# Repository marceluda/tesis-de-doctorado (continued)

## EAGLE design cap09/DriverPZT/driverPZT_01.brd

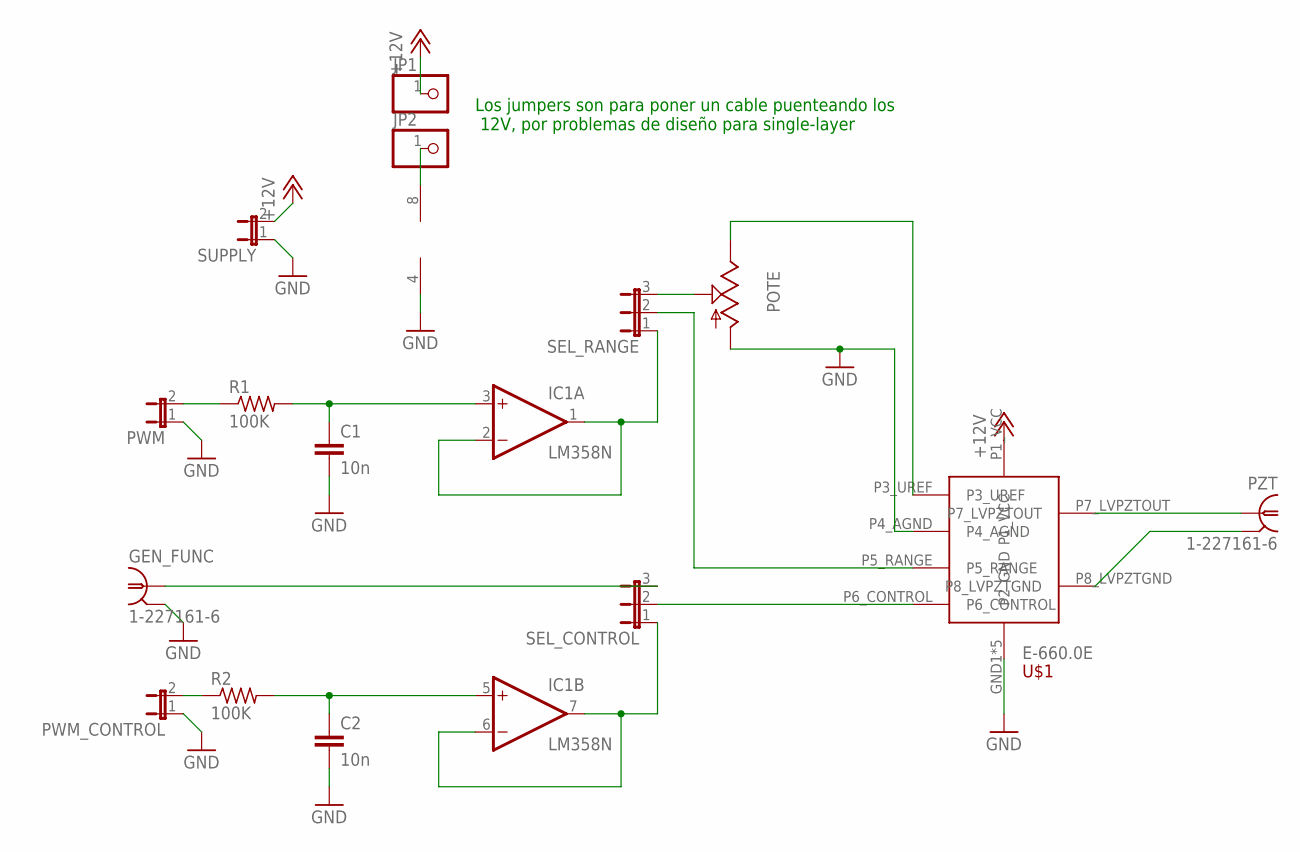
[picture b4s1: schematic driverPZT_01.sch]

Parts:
C1, C2: 10n; C050-075X075
GEN_FUNC: 1-227161-6; AMP_227161
IC1: LM358N; DIL08
JP1, JP2: PINHD-1X1; 1X01
POTE: TRIM_US-B64Y; B64Y
PWM: JP1E; JP1
PWM_CONTROL: JP1E; JP1
PZT: 1-227161-6; AMP_227161
R1, R2: 100K; 0207/12
SEL_CONTROL: JP2E; JP2
SEL_RANGE: JP2E; JP2
SUPPLY: JP1E; JP1
U$1: E-660.0E

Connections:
+12V: JP1.1, SUPPLY.2, U$1.P1_VCC
GF: SEL_RANGE.2, U$1.P5_RANGE
GND: C1.2, C2.2, GEN_FUNC.2, IC1.4 (V-), POTE.A, PWM.1, PWM_CONTROL.1, SUPPLY.1, U$1.GND1 (P2_GND), U$1.GND2 (P2_GND), U$1.GND3 (P2_GND), U$1.GND4 (P2_GND), U$1.P2_GND, U$1.P4_AGND
unnamed: PWM_CONTROL.2, R2.1
unnamed: C2.1, IC1.5 (+IN), R2.2
unnamed: SEL_CONTROL.2, U$1.P6_CONTROL
unnamed: GEN_FUNC.1, SEL_CONTROL.3
unnamed: C1.1, IC1.3 (+IN), R1.2
unnamed: IC1.1 (OUT), IC1.2 (-IN), SEL_RANGE.1
unnamed: POTE.E, U$1.P3_UREF
unnamed: IC1.6 (-IN), IC1.7 (OUT), SEL_CONTROL.1
unnamed: IC1.8 (V+), JP2.1
POTE: POTE.S, SEL_RANGE.3
PWM: PWM.2, R1.1
PZT: PZT.1, U$1.P7_LVPZTOUT
PZTGND: PZT.2, U$1.P8_LVPZTGND

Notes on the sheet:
Los jumpers son para poner un cable puenteando los 12V, por problemas de diseño para single-layer

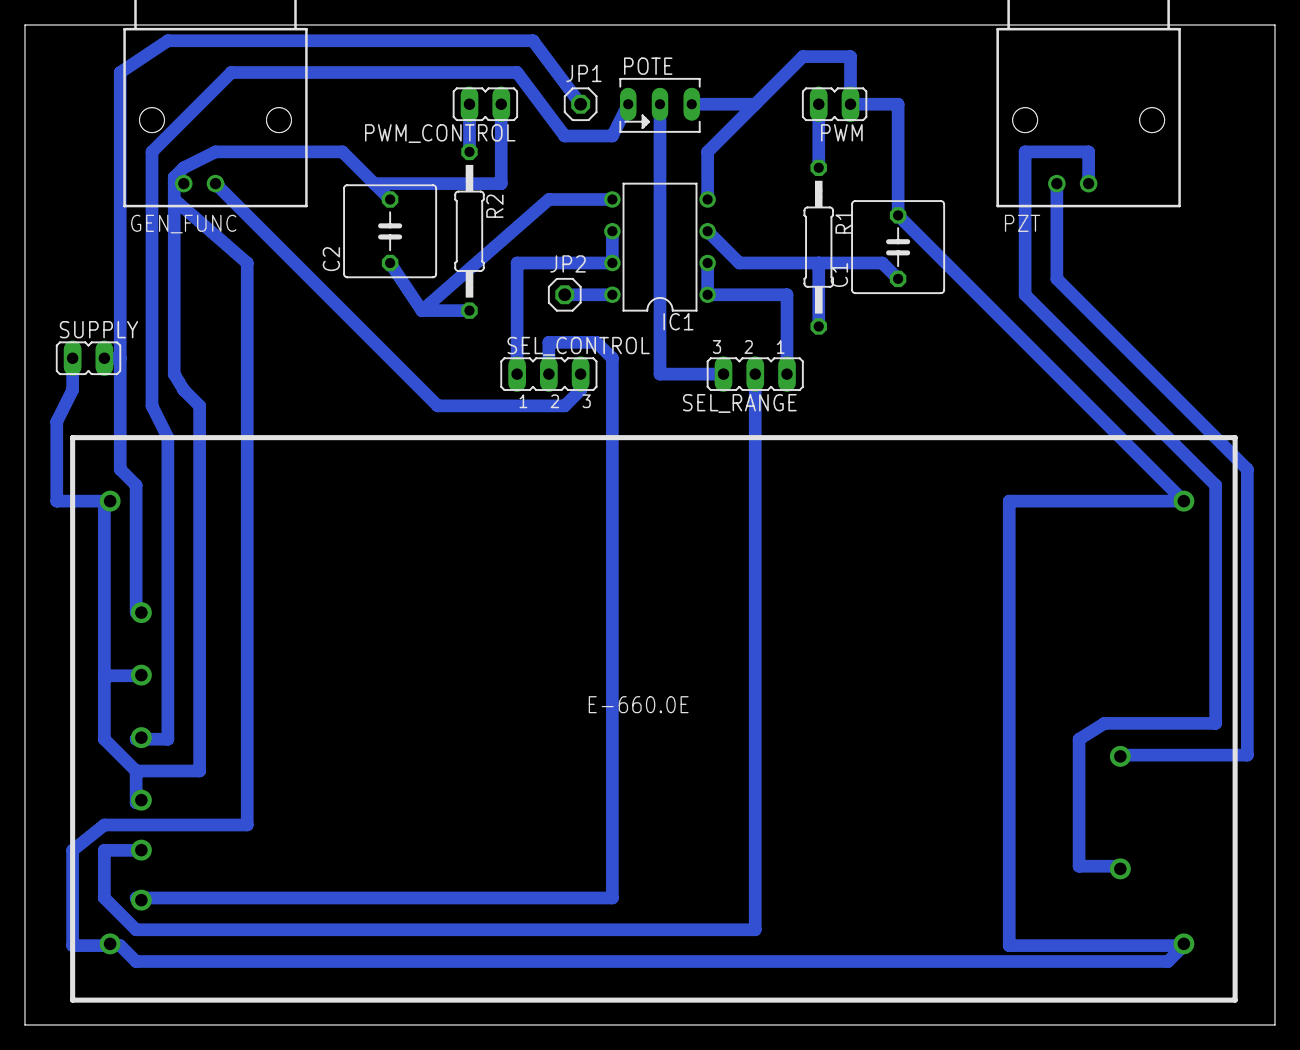
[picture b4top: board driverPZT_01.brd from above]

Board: 2 copper layers, 100.0 x 80.0 mm, 16 parts (0 on the bottom side), 16 nets.

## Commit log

2021-07-25 estrcutura cap06
2021-07-25 graficos
2021-07-25 img 02
2021-08-01 cap07
2021-08-02 cap7++
2021-08-07 cap08 +
2021-08-10 cap08 ++
2021-08-10 fix git ignore
2021-08-17 driver_PZT++
2021-08-17 fix2
2021-08-17 dirver_PZT
2021-08-17 Driver Corriente
2021-08-17 TEC ++
2021-08-17 arduino++
2021-08-18 cmd center
2021-08-18 listo 09 por ahora
2021-08-21 anim
2021-09-11 cap15
2021-09-11 cap15++
2021-09-25 18++
2021-09-29 cap19++
2021-09-29 19++
